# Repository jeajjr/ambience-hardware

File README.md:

# Ambience hardware

## The project

Project page: [Ambience](https://jeajjr.github.io/ambience/)

## Hardware project

This repository contains the Eagle schematic and board layout of the project.

Software used: Autodesk Eagle 9

## Layout

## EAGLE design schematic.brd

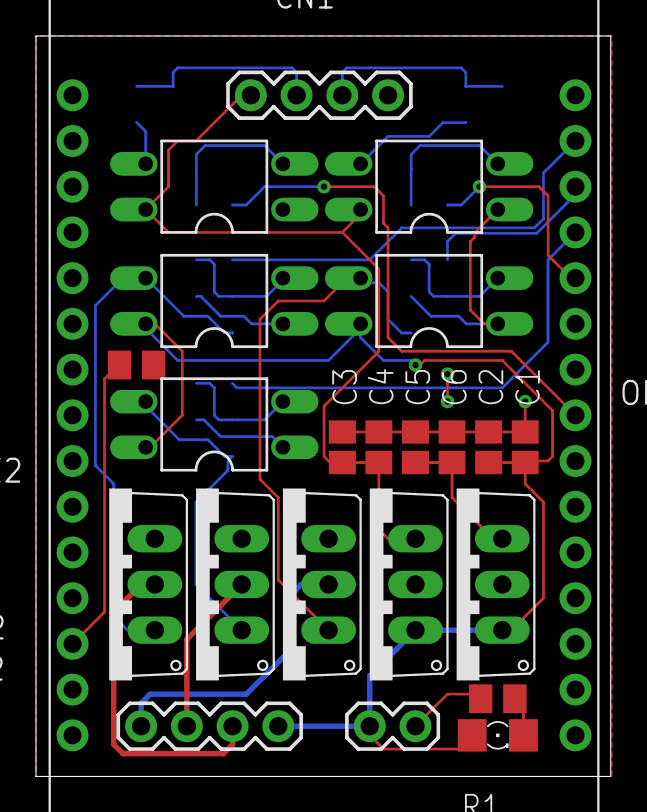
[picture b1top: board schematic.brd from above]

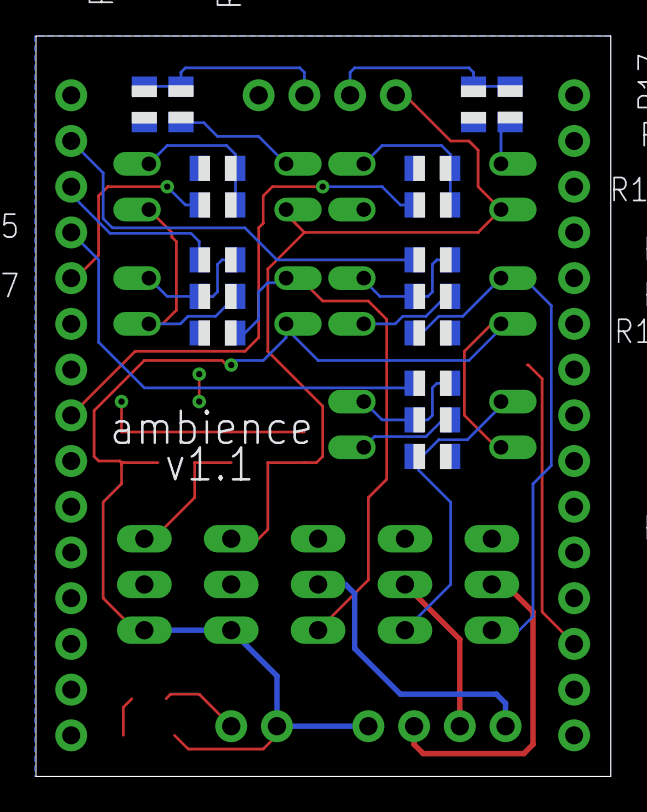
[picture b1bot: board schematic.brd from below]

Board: 2 copper layers, 31.9 x 41.1 mm, 40 parts (17 on the bottom side), 26 nets.

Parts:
C1, C2, C3, C4, C5, C6: C0805
CN1, CN2: 1X4-BIG; 1X04-BIG
IC3, IC4: 78TO220; TO220V
LED1: 1206
OK1, OK2, OK3, OK4, OK5: PC817; DIL04
Q1, Q2, Q3: TO220V
R1, R19: 1k; M0805
R2, R3, R4, R8, R9, R10, R11, R12, R17, R18: 10k; R0805
R5, R6, R7, R13, R14, R15, R16: 1k; R0805
U$1: ESP8266; ESP8266-NODEMCU
U$2: HEADER-2X1

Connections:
+3V3: C5.1, C6.1, IC4.3, OK1.1, OK2.1, OK3.1, OK4.1, OK5.1, R2.1, R3.1, R4.1, R19.1, U$1.P$11, U$1.P$16, U$1.P$25
+5V: C3.1, C4.1, CN1.1, IC3.3, OK4.4, OK5.4
+12V: C1.1, C2.1, CN2.4, IC3.1, IC4.1, LED1.A, OK1.4, OK2.4, OK3.4, U$2.1
CTRL_A_3V3: R16.2, U$1.P$23
CTRL_A_5V: CN1.2, R13.1, R17.2
CTRL_B: R5.2, U$1.P$29
CTRL_B_3V3: R15.2, U$1.P$26
CTRL_B_5V: CN1.3, R14.1, R18.2
CTRL_G: R6.2, U$1.P$27
CTRL_R: R7.2, U$1.P$28
GND: C1.2, C2.2, C3.2, C4.2, C5.2, C6.2, CN1.4, IC3.2, IC4.2, Q1.3, Q2.3, Q3.3, R1.2, R8.1, R9.1, R10.1, R11.1, R12.1, R17.1, R18.1, U$1.P$2, U$1.P$10, U$1.P$14, U$1.P$17, U$1.P$24, U$2.2
unnamed: OK1.2, R2.2, R7.1
unnamed: LED1.C, R1.1
unnamed: OK2.2, R3.2, R6.1
unnamed: OK3.2, R4.2, R5.1
unnamed: OK3.3, Q1.1, R10.2
unnamed: OK2.3, Q2.1, R8.2
unnamed: OK1.3, Q3.1, R9.2
unnamed: R19.2, U$1.P$13
unnamed: OK5.3, R14.2
unnamed: OK5.2, R11.2, R15.1
unnamed: OK4.2, R12.2, R16.1
unnamed: OK4.3, R13.2
POW_B: CN2.3, Q1.2
POW_G: CN2.2, Q2.2
POW_R: CN2.1, Q3.2

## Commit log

2017-08-22 Created schematic; Pre-organized components on PCB
2017-08-30 Initial board layout
2017-08-30 Added board alongation for J4 connector
2017-08-30 Removed components names from board
2018-11-15 Inverted polarity of LED control on optocouplers
2020-05-24 Updated board; enhanced schematics organization
2021-05-04 Started v1.1 board layout; updated schematics
